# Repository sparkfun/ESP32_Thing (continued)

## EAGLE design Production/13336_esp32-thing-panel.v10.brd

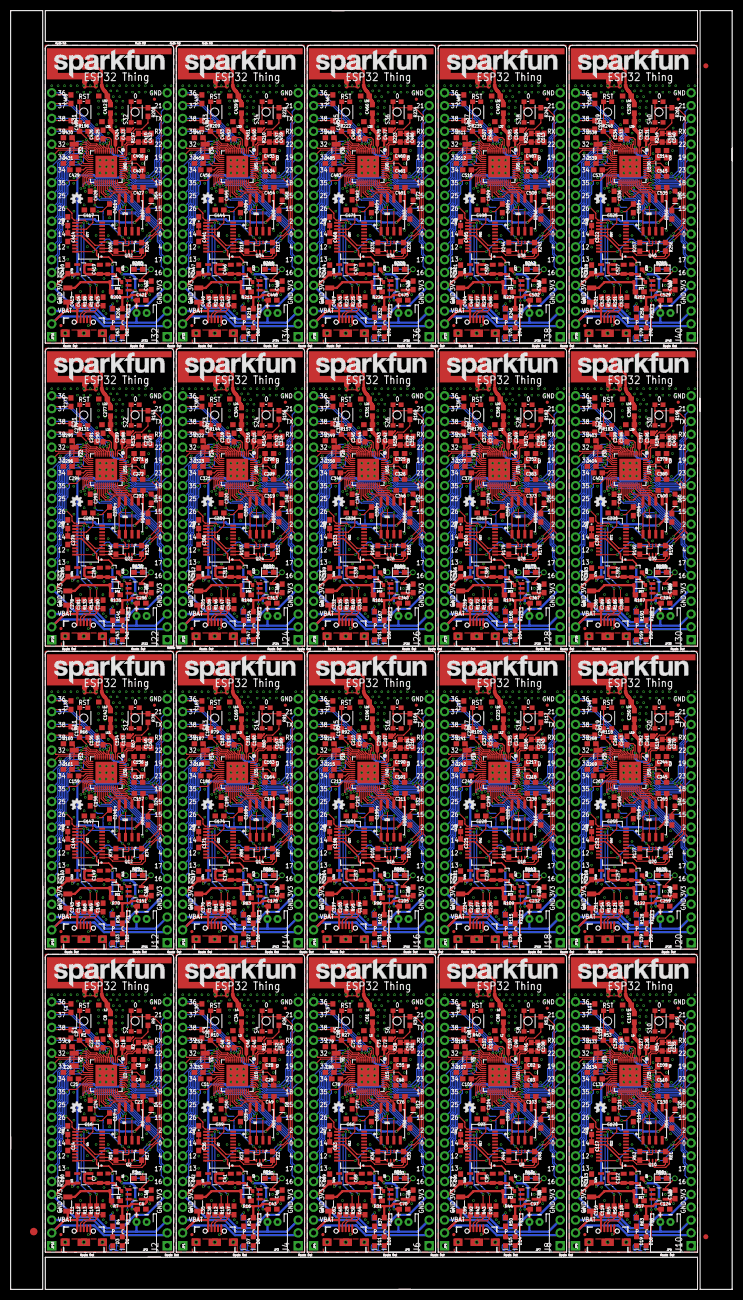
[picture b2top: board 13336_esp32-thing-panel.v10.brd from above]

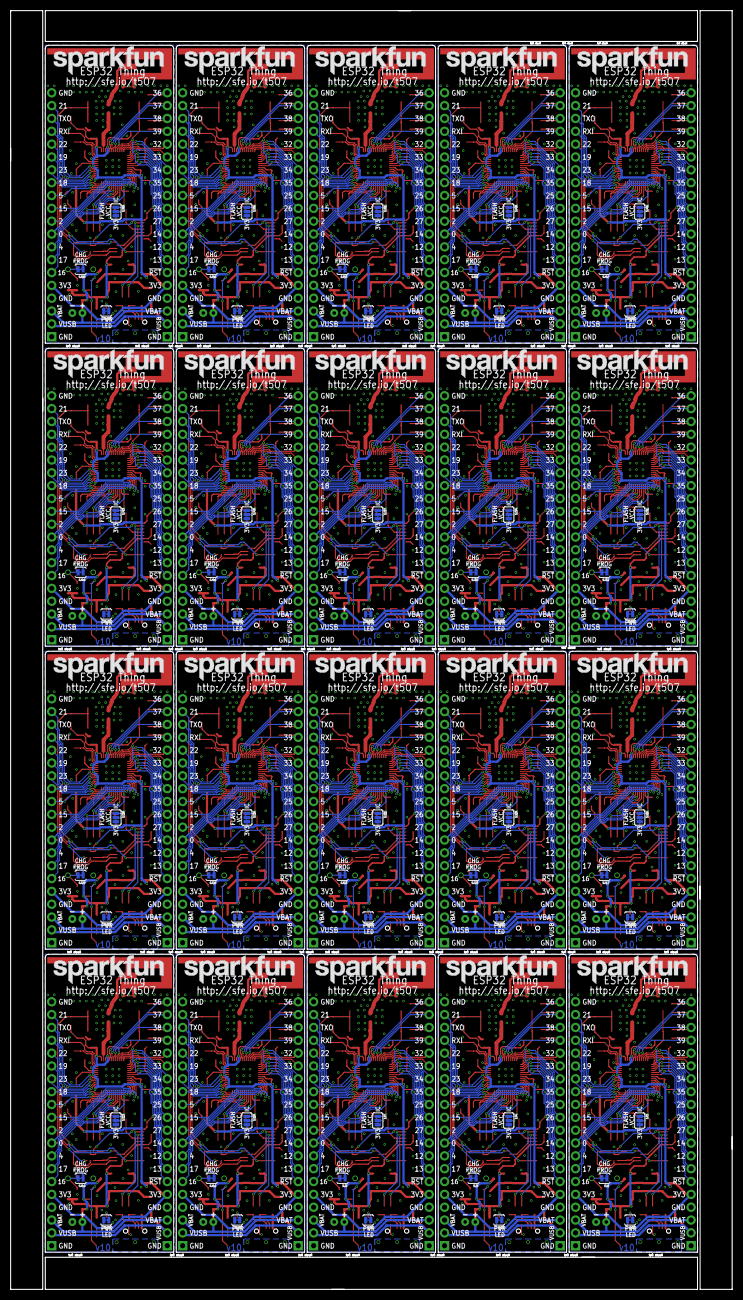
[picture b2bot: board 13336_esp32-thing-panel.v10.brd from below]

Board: 2 copper layers, 142.7 x 253.0 mm, 1423 parts (80 on the bottom side), 1320 nets.

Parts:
C1, C2, C30, C31, C57, C58, C84, C85, C111, C112, C138, C139, C165, C166, C192, C193, C219, C220, C246, C247, C273, C274, C300, C301, C327, C328, C354, C355, C381, C382, C408, C409, C435, C436, C462, C463, C489, C490, C516, C517: 270pF; 0603
C3, C4, C28, C29, C55, C56, C82, C83, C109, C110, C136, C137, C163, C164, C190, C191, C217, C218, C244, C245, C271, C272, C298, C299, C325, C326, C352, C353, C379, C380, C406, C407, C433, C434, C460, C461, C487, C488, C514, C515: 10pF; 0603
C5, C32, C59, C86, C113, C140, C167, C194, C221, C248, C275, C302, C329, C356, C383, C410, C437, C464, C491, C518: 10nF; 0603
C6, C19, C43, C44, C70, C71, C97, C98, C124, C125, C151, C152, C178, C179, C205, C206, C232, C233, C259, C260, C286, C287, C313, C314, C340, C341, C367, C368, C394, C395, C421, C422, C448, C449, C475, C476, C502, C503, C529, C530: 4.7uF; 0603
C7, C41, C68, C95, C122, C149, C176, C203, C230, C257, C284, C311, C338, C365, C392, C419, C446, C473, C500, C527: 1.0uF; 0805
C8, C34, C61, C88, C115, C142, C169, C196, C223, C250, C277, C304, C331, C358, C385, C412, C439, C466, C493, C520: 5.6pF; 0603
C9, C26, C52, C53, C79, C80, C106, C107, C133, C134, C160, C161, C187, C188, C214, C215, C241, C242, C268, C269, C295, C296, C322, C323, C349, C350, C376, C377, C403, C404, C430, C431, C457, C458, C484, C485, C511, C512, C538, C539: 15pF; 0603
C10, C42, C69, C96, C123, C150, C177, C204, C231, C258, C285, C312, C339, C366, C393, C420, C447, C474, C501, C528: 2.2uF; 0603
C11, C14, C16, C17, C20, C21, C23, C25, C33, C35, C36, C39, C46, C47, C49, C51, C60, C62, C63, C66, C73, C74, C76, C78, C87, C89, C90, C93, C100, C101, C103, C105, C114, C116, C117, C120, C127, C128, C130, C132, C141, C143, C144, C147, C154, C155, C157, C159, C168, C170, C171, C174, C181, C182, C184, C186, C195, C197, C198, C201, C208, C209, C211, C213, C222, C224, C225, C228, C235, C236, C238, C240, C249, C251, C252, C255, C262, C263, C265, C267, C276, C278, C279, C282, C289, C290, C292, C294, C303, C305, C306, C309, C316, C317, C319, C321, C330, C332, C333, C336, C343, C344, C346, C348, C357, C359, C360, C363, C370, C371, C373, C375, C384, C386, C387, C390, C397, C398, C400, C402, C411, C413, C414, C417, C424, C425, C427, C429, C438, C440, C441, C444, C451, C452, C454, C456, C465, C467, C468, C471, C478, C479, C481, C483, C492, C494, C495, C498, C505, C506, C508, C510, C519, C521, C522, C525, C532, C533, C535, C537: 0.1uF; 0603
C12, C13, C37, C38, C64, C65, C91, C92, C118, C119, C145, C146, C172, C173, C199, C200, C226, C227, C253, C254, C280, C281, C307, C308, C334, C335, C361, C362, C388, C389, C415, C416, C442, C443, C469, C470, C496, C497, C523, C524: 47pF; 0603
C15, C40, C67, C94, C121, C148, C175, C202, C229, C256, C283, C310, C337, C364, C391, C418, C445, C472, C499, C526: 4.7uF; 0603-CAP
C18, C45, C72, C99, C126, C153, C180, C207, C234, C261, C288, C315, C342, C369, C396, C423, C450, C477, C504, C531: 100pF; 0603
C22, C48, C75, C102, C129, C156, C183, C210, C237, C264, C291, C318, C345, C372, C399, C426, C453, C480, C507, C534: 10uF; 0603
C24, C50, C77, C104, C131, C158, C185, C212, C239, C266, C293, C320, C347, C374, C401, C428, C455, C482, C509, C536: 1.0uF; 0603
C27, C54, C81, C108, C135, C162, C189, C216, C243, C270, C297, C324, C351, C378, C405, C432, C459, C486, C513, C540: 3.0nF; 0603
D1, D6, D10, D14, D18, D22, D26, D30, D34, D38, D42, D46, D50, D54, D58, D62, D66, D70, D74, D78: Yellow; LED-0603
D2, D5, D9, D13, D17, D21, D25, D29, D33, D37, D41, D45, D49, D53, D57, D61, D65, D69, D73, D77: BAT20J; SOD-323
D3, D7, D11, D15, D19, D23, D27, D31, D35, D39, D43, D47, D51, D55, D59, D63, D67, D71, D75, D79: RED; LED-0603
D4, D8, D12, D16, D20, D24, D28, D32, D36, D40, D44, D48, D52, D56, D60, D64, D68, D72, D76, D80: BLUE; LED-0603
E1, E2, E3, E4, E5, E6, E7, E8, E9, E10, E11, E12, E13, E14, E15, E16, E17, E18, E19, E20: ANTENNA; TRACE_ANTENNA_2.4GHZ_25.7MM_TUNED
E$1: FIDUCIAL-1.5X3
E$7, E$8: FIDUCIAL-1X2
F1, F2, F3, F4, F5, F6, F7, F8, F9, F10, F11, F12, F13, F14, F15, F16, F17, F18, F19, F20: 500mA; PTC-1206
FD1, FD2, FD3, FD4, FD5, FD6, FD7, FD8, FD9, FD10, FD11, FD12, FD13, FD14, FD15, FD16, FD17, FD18, FD19, FD20, FD21, FD22, FD23, FD24, FD25, FD26, FD27, FD28, FD29, FD30, FD31, FD32, FD33, FD34, FD35, FD36, FD37, FD38, FD39, FD40: FIDUCIALUFIDUCIAL; MICRO-FIDUCIAL
J1, J2, J3, J4, J5, J6, J7, J8, J9, J10, J11, J12, J13, J14, J15, J16, J17, J18, J19, J20, J21, J22, J23, J24, J25, J26, J27, J28, J29, J30, J31, J32, J33, J34, J35, J36, J37, J38, J39, J40: 1X20_NOSILK
JP1, JP4, JP6, JP8, JP10, JP12, JP14, JP15, JP17, JP19, JP21, JP23, JP25, JP27, JP29, JP31, JP33, JP35, JP37, JP39: USB-B-MICRO-SMD_V03
JP2, JP3, JP5, JP7, JP9, JP11, JP13, JP16, JP18, JP20, JP22, JP24, JP26, JP28, JP30, JP32, JP34, JP36, JP38, JP40: LiPo; JST-2-PTH
L1, L2, L3, L4, L5, L6, L7, L8, L9, L10, L11, L12, L13, L14, L15, L16, L17, L18, L19, L20, L21, L22, L23, L24, L25, L26, L27, L28, L29, L30, L31, L32, L33, L34, L35, L36, L37, L38, L39, L40: DNP; 0603
LOGO1, LOGO3, LOGO4, LOGO6, LOGO7, LOGO9, LOGO10, LOGO12, LOGO13, LOGO15, LOGO16, LOGO18, LOGO19, LOGO21, LOGO22, LOGO24, LOGO25, LOGO27, LOGO28, LOGO30, LOGO31, LOGO33, LOGO34, LOGO36, LOGO37, LOGO39, LOGO40, LOGO42, LOGO43, LOGO45, LOGO46, LOGO48, LOGO49, LOGO51, LOGO52, LOGO54, LOGO55, LOGO57, LOGO58, LOGO60: SFE_LOGO_NAME.2_INCH; SFE_LOGO_NAME_.2
LOGO2, LOGO5, LOGO8, LOGO11, LOGO14, LOGO17, LOGO20, LOGO23, LOGO26, LOGO29, LOGO32, LOGO35, LOGO38, LOGO41, LOGO44, LOGO47, LOGO50, LOGO53, LOGO56, LOGO59: OSHW-LOGOMINI; OSHW-LOGO-MINI
Q1, Q3, Q5, Q7, Q9, Q11, Q13, Q15, Q17, Q19, Q21, Q23, Q25, Q27, Q29, Q31, Q33, Q35, Q37, Q39: 2.5A/30V; SOT23-3
Q2, Q4, Q6, Q8, Q10, Q12, Q14, Q16, Q18, Q20, Q22, Q24, Q26, Q28, Q30, Q32, Q34, Q36, Q38, Q40: MBT3904DW1T1; SC70-6
R1, R7, R9, R10, R16, R17, R18, R22, R23, R26, R27, R31, R35, R36, R39, R40, R44, R48, R49, R52, R53, R57, R61, R62, R65, R66, R70, R74, R75, R78, R79, R83, R87, R88, R91, R92, R96, R100, R101, R104, R105, R109, R113, R114, R117, R118, R122, R126, R127, R130, R131, R135, R139, R140, R143, R144, R148, R152, R153, R156, R157, R161, R165, R166, R169, R170, R174, R178, R179, R182, R183, R187, R191, R192, R195, R196, R200, R204, R205, R208, R209, R213, R217, R218, R221, R222, R226, R230, R231, R234, R235, R239, R243, R244, R247, R248, R252, R256, R257, R260: 10k; 0603
R2, R11, R28, R41, R54, R67, R80, R93, R106, R119, R132, R145, R158, R171, R184, R197, R210, R223, R236, R249: 20k; 0603
R3, R4, R19, R24, R32, R37, R45, R50, R58, R63, R71, R76, R84, R89, R97, R102, R110, R115, R123, R128, R136, R141, R149, R154, R162, R167, R175, R180, R188, R193, R201, R206, R214, R219, R227, R232, R240, R245, R253, R258: 1K; 0603
R5, R21, R34, R47, R60, R73, R86, R99, R112, R125, R138, R151, R164, R177, R190, R203, R216, R229, R242, R255: DNP; 1/6W-RES
R6, R20, R33, R46, R59, R72, R85, R98, R111, R124, R137, R150, R163, R176, R189, R202, R215, R228, R241, R254: 2.0k; 0603
R8, R25, R38, R51, R64, R77, R90, R103, R116, R129, R142, R155, R168, R181, R194, R207, R220, R233, R246, R259: 330; 0603
R12, R13, R14, R15, R29, R30, R42, R43, R55, R56, R68, R69, R81, R82, R94, R95, R107, R108, R120, R121, R133, R134, R146, R147, R159, R160, R172, R173, R185, R186, R198, R199, R211, R212, R224, R225, R237, R238, R250, R251: 27; 0603
S1, S3, S5, S7, S9, S11, S13, S15, S17, S19, S21, S23, S25, S27, S29, S31, S33, S35, S37, S39: RESET; TACTILE_SWITCH_SMD_4.6X2.8MM
S2, S4, S6, S8, S10, S12, S14, S16, S18, S20, S22, S24, S26, S28, S30, S32, S34, S36, S38, S40: BTN-0; TACTILE_SWITCH_SMD_4.6X2.8MM
SJ1, SJ2, SJ5, SJ6, SJ8, SJ9, SJ11, SJ12, SJ14, SJ15, SJ17, SJ18, SJ20, SJ21, SJ23, SJ24, SJ26, SJ27, SJ29, SJ30, SJ32, SJ33, SJ35, SJ36, SJ38, SJ39, SJ41, SJ42, SJ44, SJ45, SJ47, SJ48, SJ50, SJ51, SJ53, SJ54, SJ56, SJ57, SJ59, SJ60: JUMPER-PAD-2-NC_BY_TRACE; PAD-JUMPER-2-NC_BY_TRACE_YES_SILK
SJ3, SJ4, SJ7, SJ10, SJ13, SJ16, SJ19, SJ22, SJ25, SJ28, SJ31, SJ34, SJ37, SJ40, SJ43, SJ46, SJ49, SJ52, SJ55, SJ58: PAD-JUMPER-3-2OF3_NC_BY_TRACE_YES_SILK_FULL_BOX
U1, U8, U13, U18, U23, U28, U33, U38, U43, U48, U53, U58, U63, U68, U73, U78, U83, U88, U93, U98: MCP73831; SOT23-5
U2, U10, U15, U20, U25, U30, U35, U40, U45, U50, U55, U60, U65, U70, U75, U80, U85, U90, U95, U100: ESP3212; QFN48-0.4MM
U3, U9, U14, U19, U24, U29, U34, U39, U44, U49, U54, U59, U64, U69, U74, U79, U84, U89, U94, U99: AP2112K-3.3V; SOT23-5
U4, U7, U12, U17, U22, U27, U32, U37, U42, U47, U52, U57, U62, U67, U72, U77, U82, U87, U92, U97: FT231XS; SSOP20_L
U5, U6, U11, U16, U21, U26, U31, U36, U41, U46, U51, U56, U61, U66, U71, U76, U81, U86, U91, U96: W25Q32FVSS; SOIC-8
Y1, Y3, Y5, Y7, Y9, Y11, Y13, Y15, Y17, Y19, Y21, Y23, Y25, Y27, Y29, Y31, Y33, Y35, Y37, Y39: 26MHz; CRYSTAL-SMD-3.2X2.5
Y2, Y4, Y6, Y8, Y10, Y12, Y14, Y16, Y18, Y20, Y22, Y24, Y26, Y28, Y30, Y32, Y34, Y36, Y38, Y40: 32.768kHz; CRYSTAL-SMD-3.2X1.5MM

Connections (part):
0: J2.9, Q2.6, R9.1, S2.3, S2.4, U2.23
1: J3.14, U10.10
2: J2.10, U2.22
3: J3.13, U10.11
3.3V: C10.1, C18.1, C20.1, C21.1, C22.1, C23.1, C25.1, J1.5, J2.5, R1.2, R9.2, SJ2.2, SJ3.3, U2.1, U2.3, U2.4, U2.19, U2.37, U2.43, U2.46, U3.5
3.3V1: C42.1, C45.1, C46.1, C47.1, C48.1, C49.1, C51.1, J3.5, J4.5, R10.2, R26.2, SJ4.3, SJ6.2, U9.5, U10.1, U10.3, U10.4, U10.19, U10.37, U10.43, U10.46
3.3V2: C69.1, C72.1, C73.1, C74.1, C75.1, C76.1, C78.1, J5.5, J6.5, R27.2, R39.2, SJ7.3, SJ9.2, U14.5, U15.1, U15.3, U15.4, U15.19, U15.37, U15.43, U15.46
3.3V3: C96.1, C99.1, C100.1, C101.1, C102.1, C103.1, C105.1, J7.5, J8.5, R40.2, R52.2, SJ10.3, SJ12.2, U19.5, U20.1, U20.3, U20.4, U20.19, U20.37, U20.43, U20.46
3.3V4: C123.1, C126.1, C127.1, C128.1, C129.1, C130.1, C132.1, J9.5, J10.5, R53.2, R65.2, SJ13.3, SJ15.2, U24.5, U25.1, U25.3, U25.4, U25.19, U25.37, U25.43, U25.46
3.3V5: C150.1, C153.1, C154.1, C155.1, C156.1, C157.1, C159.1, J11.5, J12.5, R66.2, R78.2, SJ16.3, SJ18.2, U29.5, U30.1, U30.3, U30.4, U30.19, U30.37, U30.43, U30.46
3.3V6: C177.1, C180.1, C181.1, C182.1, C183.1, C184.1, C186.1, J13.5, J14.5, R79.2, R91.2, SJ19.3, SJ21.2, U34.5, U35.1, U35.3, U35.4, U35.19, U35.37, U35.43, U35.46
3.3V7: C204.1, C207.1, C208.1, C209.1, C210.1, C211.1, C213.1, J15.5, J16.5, R92.2, R104.2, SJ22.3, SJ24.2, U39.5, U40.1, U40.3, U40.4, U40.19, U40.37, U40.43, U40.46
3.3V8: C231.1, C234.1, C235.1, C236.1, C237.1, C238.1, C240.1, J17.5, J18.5, R105.2, R117.2, SJ25.3, SJ27.2, U44.5, U45.1, U45.3, U45.4, U45.19, U45.37, U45.43, U45.46
3.3V9: C258.1, C261.1, C262.1, C263.1, C264.1, C265.1, C267.1, J19.5, J20.5, R118.2, R130.2, SJ28.3, SJ30.2, U49.5, U50.1, U50.3, U50.4, U50.19, U50.37, U50.43, U50.46
3.3V10: C285.1, C288.1, C289.1, C290.1, C291.1, C292.1, C294.1, J21.5, J22.5, R131.2, R143.2, SJ31.3, SJ33.2, U54.5, U55.1, U55.3, U55.4, U55.19, U55.37, U55.43, U55.46
3.3V11: C312.1, C315.1, C316.1, C317.1, C318.1, C319.1, C321.1, J23.5, J24.5, R144.2, R156.2, SJ34.3, SJ36.2, U59.5, U60.1, U60.3, U60.4, U60.19, U60.37, U60.43, U60.46
3.3V12: C339.1, C342.1, C343.1, C344.1, C345.1, C346.1, C348.1, J25.5, J26.5, R157.2, R169.2, SJ37.3, SJ39.2, U64.5, U65.1, U65.3, U65.4, U65.19, U65.37, U65.43, U65.46
3.3V13: C366.1, C369.1, C370.1, C371.1, C372.1, C373.1, C375.1, J27.5, J28.5, R170.2, R182.2, SJ40.3, SJ42.2, U69.5, U70.1, U70.3, U70.4, U70.19, U70.37, U70.43, U70.46
3.3V14: C393.1, C396.1, C397.1, C398.1, C399.1, C400.1, C402.1, J29.5, J30.5, R183.2, R195.2, SJ43.3, SJ45.2, U74.5, U75.1, U75.3, U75.4, U75.19, U75.37, U75.43, U75.46
3.3V15: C420.1, C423.1, C424.1, C425.1, C426.1, C427.1, C429.1, J31.5, J32.5, R196.2, R208.2, SJ46.3, SJ48.2, U79.5, U80.1, U80.3, U80.4, U80.19, U80.37, U80.43, U80.46
3.3V16: C447.1, C450.1, C451.1, C452.1, C453.1, C454.1, C456.1, J33.5, J34.5, R209.2, R221.2, SJ49.3, SJ51.2, U84.5, U85.1, U85.3, U85.4, U85.19, U85.37, U85.43, U85.46
3.3V17: C474.1, C477.1, C478.1, C479.1, C480.1, C481.1, C483.1, J35.5, J36.5, R222.2, R234.2, SJ52.3, SJ54.2, U89.5, U90.1, U90.3, U90.4, U90.19, U90.37, U90.43, U90.46
3.3V18: C501.1, C504.1, C505.1, C506.1, C507.1, C508.1, C510.1, J37.5, J38.5, R235.2, R247.2, SJ55.3, SJ57.2, U94.5, U95.1, U95.3, U95.4, U95.19, U95.37, U95.43, U95.46
3.3V19: C528.1, C531.1, C532.1, C533.1, C534.1, C535.1, C537.1, J39.5, J40.5, R248.2, R260.2, SJ58.3, SJ60.2, U99.5, U100.1, U100.3, U100.4, U100.19, U100.37, U100.43, U100.46
3.3V_F: C16.1, U4.3, U4.13, U4.14
3.3V_F1: C39.1, U7.3, U7.13, U7.14
3.3V_F2: C66.1, U12.3, U12.13, U12.14
3.3V_F3: C93.1, U17.3, U17.13, U17.14
3.3V_F4: C120.1, U22.3, U22.13, U22.14
3.3V_F5: C147.1, U27.3, U27.13, U27.14
3.3V_F6: C174.1, U32.3, U32.13, U32.14
3.3V_F7: C201.1, U37.3, U37.13, U37.14
3.3V_F8: C228.1, U42.3, U42.13, U42.14
3.3V_F9: C255.1, U47.3, U47.13, U47.14
3.3V_F10: C282.1, U52.3, U52.13, U52.14
3.3V_F11: C309.1, U57.3, U57.13, U57.14
3.3V_F12: C336.1, U62.3, U62.13, U62.14
3.3V_F13: C363.1, U67.3, U67.13, U67.14
3.3V_F14: C390.1, U72.3, U72.13, U72.14
3.3V_F15: C417.1, U77.3, U77.13, U77.14
3.3V_F16: C444.1, U82.3, U82.13, U82.14
3.3V_F17: C471.1, U87.3, U87.13, U87.14
3.3V_F18: C498.1, U92.3, U92.13, U92.14
3.3V_F19: C525.1, U97.3, U97.13, U97.14
4: J2.8, U2.24
5: D4.A, J2.12, U2.34
6: C31.2, J3.17, U10.8
7: C31.1, J3.18, U10.7
8: C30.2, J3.20, U10.5
9: C30.1, J3.19, U10.6
10: J4.11, U10.21
11: J3.9, U10.17
12: J1.8, U2.18
13: J1.7, U2.20
14: J1.9, U2.17
15: J2.11, U2.21
16: J2.6, U2.25
17: J2.7, U2.27
18: J2.13, U2.35
19: J2.15, U2.38
20: J3.7, U10.20
21: J2.19, U2.42
22: J2.16, U2.39
23: J2.14, U2.36
24: J3.8, U10.18
25: J1.12, U2.14
26: J1.11, U2.15
27: J1.10, U2.16
28: J3.10, U10.16
29: J3.11, U10.15
30: J4.16, U10.39
31: J4.19, U10.42
32: J4.15, U10.38
32K_XN: C26.2, J1.15, U2.13, Y2.P$2
32K_XN1: C53.2, J3.15, U10.13, Y4.P$2
32K_XN2: C80.2, J5.15, U15.13, Y6.P$2
32K_XN3: C107.2, J7.15, U20.13, Y8.P$2
32K_XN4: C134.2, J9.15, U25.13, Y10.P$2
32K_XN5: C161.2, J11.15, U30.13, Y12.P$2
32K_XN6: C188.2, J13.15, U35.13, Y14.P$2
32K_XN7: C215.2, J15.15, U40.13, Y16.P$2
32K_XN8: C242.2, J17.15, U45.13, Y18.P$2
32K_XN9: C269.2, J19.15, U50.13, Y20.P$2
32K_XN10: C296.2, J21.15, U55.13, Y22.P$2
32K_XN11: C323.2, J23.15, U60.13, Y24.P$2
32K_XN12: C350.2, J25.15, U65.13, Y26.P$2
32K_XN13: C377.2, J27.15, U70.13, Y28.P$2
32K_XN14: C404.2, J29.15, U75.13, Y30.P$2
32K_XN15: C431.2, J31.15, U80.13, Y32.P$2
32K_XN16: C458.2, J33.15, U85.13, Y34.P$2
32K_XN17: C485.2, J35.15, U90.13, Y36.P$2
32K_XN18: C512.2, J37.15, U95.13, Y38.P$2
32K_XN19: C539.2, J39.15, U100.13, Y40.P$2
32K_XP: C9.2, J1.16, U2.12, Y2.P$1
32K_XP1: C52.2, J3.16, U10.12, Y4.P$1
32K_XP2: C79.2, J5.16, U15.12, Y6.P$1
32K_XP3: C106.2, J7.16, U20.12, Y8.P$1
32K_XP4: C133.2, J9.16, U25.12, Y10.P$1
32K_XP5: C160.2, J11.16, U30.12, Y12.P$1
32K_XP6: C187.2, J13.16, U35.12, Y14.P$1
32K_XP7: C214.2, J15.16, U40.12, Y16.P$1
32K_XP8: C241.2, J17.16, U45.12, Y18.P$1
32K_XP9: C268.2, J19.16, U50.12, Y20.P$1
32K_XP10: C295.2, J21.16, U55.12, Y22.P$1
32K_XP11: C322.2, J23.16, U60.12, Y24.P$1
32K_XP12: C349.2, J25.16, U65.12, Y26.P$1
32K_XP13: C376.2, J27.16, U70.12, Y28.P$1
32K_XP14: C403.2, J29.16, U75.12, Y30.P$1
32K_XP15: C430.2, J31.16, U80.12, Y32.P$1
32K_XP16: C457.2, J33.16, U85.12, Y34.P$1
32K_XP17: C484.2, J35.16, U90.12, Y36.P$1
32K_XP18: C511.2, J37.16, U95.12, Y38.P$1
32K_XP19: C538.2, J39.16, U100.12, Y40.P$1
33: J4.13, U10.35
34: J1.14, U2.10
35: J1.13, U2.11
36: C1.2, J1.20, U2.5
37: C1.1, J1.19, U2.6
38: C2.1, J1.18, U2.7
39: C2.2, J1.17, U2.8
40: J4.6, U10.25
41: D8.A, J4.12, U10.34
42: J4.8, U10.24
43: J4.10, U10.22
44: J3.12, U10.14
45: J4.9, Q4.6, R26.1, S4.3, S4.4, U10.23
46: J4.7, U10.27
47: J4.14, U10.36
48: J5.14, U15.10
49: J5.13, U15.11
50: C58.2, J5.17, U15.8
51: C58.1, J5.18, U15.7
52: C57.2, J5.20, U15.5
53: C57.1, J5.19, U15.6
54: J6.11, U15.21
55: J5.9, U15.17
56: J5.7, U15.20
57: J5.8, U15.18
58: J5.10, U15.16
59: J5.11, U15.15
60: J6.16, U15.39
61: J6.19, U15.42
62: J6.15, U15.38
63: J6.13, U15.35
64: J6.6, U15.25
65: D12.A, J6.12, U15.34
66: J6.8, U15.24
67: J6.10, U15.22
68: J5.12, U15.14
69: J6.9, Q6.6, R39.1, S6.3, S6.4, U15.23
70: J6.7, U15.27
71: J6.14, U15.36
72: J7.14, U20.10
73: J7.13, U20.11
74: C85.2, J7.17, U20.8
75: C85.1, J7.18, U20.7
76: C84.2, J7.20, U20.5
77: C84.1, J7.19, U20.6
78: J8.11, U20.21
79: J7.9, U20.17
80: J7.7, U20.20
81: J7.8, U20.18
82: J7.10, U20.16
83: J7.11, U20.15
84: J8.16, U20.39
85: J8.19, U20.42
86: J8.15, U20.38
87: J8.13, U20.35
88: J8.6, U20.25
89: D16.A, J8.12, U20.34
90: J8.8, U20.24
91: J8.10, U20.22
92: J7.12, U20.14
93: J8.9, Q8.6, R52.1, S8.3, S8.4, U20.23
94: J8.7, U20.27
95: J8.14, U20.36
96: J9.14, U25.10
97: J9.13, U25.11
98: C112.2, J9.17, U25.8
99: C112.1, J9.18, U25.7
100: C111.2, J9.20, U25.5
101: C111.1, J9.19, U25.6
102: J10.11, U25.21
103: J9.9, U25.17
104: J9.7, U25.20
105: J9.8, U25.18
106: J9.10, U25.16
107: J9.11, U25.15
108: J10.16, U25.39
109: J10.19, U25.42
110: J10.15, U25.38
111: J10.13, U25.35
112: J10.6, U25.25
113: D20.A, J10.12, U25.34
114: J10.8, U25.24
115: J10.10, U25.22
116: J9.12, U25.14
117: J10.9, Q10.6, R65.1, S10.3, S10.4, U25.23
118: J10.7, U25.27
119: J10.14, U25.36
120: J11.14, U30.10
121: J11.13, U30.11
122: C139.2, J11.17, U30.8
123: C139.1, J11.18, U30.7
124: C138.2, J11.20, U30.5
125: C138.1, J11.19, U30.6
126: J12.11, U30.21
127: J11.9, U30.17
128: J11.7, U30.20
129: J11.8, U30.18
130: J11.10, U30.16
131: J11.11, U30.15
132: J12.16, U30.39
133: J12.19, U30.42
134: J12.15, U30.38
135: J12.13, U30.35
136: J12.6, U30.25
137: D24.A, J12.12, U30.34
138: J12.8, U30.24
139: J12.10, U30.22
140: J11.12, U30.14
141: J12.9, Q12.6, R78.1, S12.3, S12.4, U30.23
142: J12.7, U30.27
143: J12.14, U30.36
144: J13.14, U35.10
145: J13.13, U35.11
146: C166.2, J13.17, U35.8
147: C166.1, J13.18, U35.7
148: C165.2, J13.20, U35.5
149: C165.1, J13.19, U35.6
150: J14.11, U35.21
151: J13.9, U35.17
152: J13.7, U35.20
153: J13.8, U35.18
154: J13.10, U35.16
155: J13.11, U35.15
156: J14.16, U35.39
157: J14.19, U35.42
158: J14.15, U35.38
159: J14.13, U35.35
160: J14.6, U35.25
161: D28.A, J14.12, U35.34
162: J14.8, U35.24
163: J14.10, U35.22
164: J13.12, U35.14
165: J14.9, Q14.6, R91.1, S14.3, S14.4, U35.23
166: J14.7, U35.27
167: J14.14, U35.36
168: J15.14, U40.10
169: J15.13, U40.11
170: C193.2, J15.17, U40.8
171: C193.1, J15.18, U40.7
172: C192.2, J15.20, U40.5
173: C192.1, J15.19, U40.6
174: J16.11, U40.21
175: J15.9, U40.17
176: J15.7, U40.20
177: J15.8, U40.18
178: J15.10, U40.16
179: J15.11, U40.15
180: J16.16, U40.39
181: J16.19, U40.42
182: J16.15, U40.38
183: J16.13, U40.35
184: J16.6, U40.25
185: D32.A, J16.12, U40.34
186: J16.8, U40.24
187: J16.10, U40.22
188: J15.12, U40.14
189: J16.9, Q16.6, R104.1, S16.3, S16.4, U40.23
190: J16.7, U40.27
191: J16.14, U40.36
192: J17.14, U45.10
193: J17.13, U45.11
194: C220.2, J17.17, U45.8
195: C220.1, J17.18, U45.7
196: C219.2, J17.20, U45.5
197: C219.1, J17.19, U45.6
198: J18.11, U45.21
199: J17.9, U45.17
200: J17.7, U45.20
201: J17.8, U45.18
202: J17.10, U45.16
203: J17.11, U45.15
204: J18.16, U45.39
205: J18.19, U45.42
206: J18.15, U45.38
207: J18.13, U45.35
208: J18.6, U45.25
209: D36.A, J18.12, U45.34
210: J18.8, U45.24
211: J18.10, U45.22
212: J17.12, U45.14
213: J18.9, Q18.6, R117.1, S18.3, S18.4, U45.23
214: J18.7, U45.27
215: J18.14, U45.36
216: J19.14, U50.10
217: J19.13, U50.11
218: C247.2, J19.17, U50.8
219: C247.1, J19.18, U50.7
220: C246.2, J19.20, U50.5
221: C246.1, J19.19, U50.6
222: J20.11, U50.21
223: J19.9, U50.17
224: J19.7, U50.20
225: J19.8, U50.18
226: J19.10, U50.16
227: J19.11, U50.15
228: J20.16, U50.39
229: J20.19, U50.42
230: J20.15, U50.38
231: J20.13, U50.35
232: J20.6, U50.25
233: D40.A, J20.12, U50.34
234: J20.8, U50.24
235: J20.10, U50.22
236: J19.12, U50.14
237: J20.9, Q20.6, R130.1, S20.3, S20.4, U50.23
238: J20.7, U50.27
239: J20.14, U50.36
240: J21.14, U55.10
241: J21.13, U55.11
242: C274.2, J21.17, U55.8
243: C274.1, J21.18, U55.7
244: C273.2, J21.20, U55.5
245: C273.1, J21.19, U55.6
246: J22.11, U55.21
247: J21.9, U55.17
248: J21.7, U55.20
249: J21.8, U55.18
250: J21.10, U55.16
251: J21.11, U55.15
252: J22.16, U55.39
253: J22.19, U55.42
254: J22.15, U55.38
255: J22.13, U55.35
256: J22.6, U55.25
257: D44.A, J22.12, U55.34
258: J22.8, U55.24
259: J22.10, U55.22
260: J21.12, U55.14
261: J22.9, Q22.6, R143.1, S22.3, S22.4, U55.23
262: J22.7, U55.27
263: J22.14, U55.36
264: J23.14, U60.10
265: J23.13, U60.11
266: C301.2, J23.17, U60.8
267: C301.1, J23.18, U60.7
268: C300.2, J23.20, U60.5
269: C300.1, J23.19, U60.6
270: J24.11, U60.21
271: J23.9, U60.17
272: J23.7, U60.20
273: J23.8, U60.18
274: J23.10, U60.16
275: J23.11, U60.15
276: J24.16, U60.39
277: J24.19, U60.42
278: J24.15, U60.38
279: J24.13, U60.35
280: J24.6, U60.25
281: D48.A, J24.12, U60.34
282: J24.8, U60.24
283: J24.10, U60.22
284: J23.12, U60.14
285: J24.9, Q24.6, R156.1, S24.3, S24.4, U60.23
286: J24.7, U60.27
287: J24.14, U60.36
288: J25.14, U65.10
289: J25.13, U65.11
290: C328.2, J25.17, U65.8
291: C328.1, J25.18, U65.7
292: C327.2, J25.20, U65.5
293: C327.1, J25.19, U65.6
294: J26.11, U65.21
295: J25.9, U65.17
296: J25.7, U65.20
297: J25.8, U65.18
298: J25.10, U65.16
299: J25.11, U65.15
300: J26.16, U65.39
301: J26.19, U65.42
302: J26.15, U65.38
303: J26.13, U65.35
304: J26.6, U65.25
305: D52.A, J26.12, U65.34
306: J26.8, U65.24
307: J26.10, U65.22
308: J25.12, U65.14
309: J26.9, Q26.6, R169.1, S26.3, S26.4, U65.23
310: J26.7, U65.27
311: J26.14, U65.36
312: J27.14, U70.10
313: J27.13, U70.11
314: C355.2, J27.17, U70.8
315: C355.1, J27.18, U70.7
316: C354.2, J27.20, U70.5
317: C354.1, J27.19, U70.6
318: J28.11, U70.21
319: J27.9, U70.17
320: J27.7, U70.20
321: J27.8, U70.18
322: J27.10, U70.16
323: J27.11, U70.15
324: J28.16, U70.39
325: J28.19, U70.42
326: J28.15, U70.38
327: J28.13, U70.35
328: J28.6, U70.25
329: D56.A, J28.12, U70.34
330: J28.8, U70.24
331: J28.10, U70.22
332: J27.12, U70.14
333: J28.9, Q28.6, R182.1, S28.3, S28.4, U70.23
334: J28.7, U70.27
335: J28.14, U70.36
336: J29.14, U75.10
337: J29.13, U75.11
338: C382.2, J29.17, U75.8
339: C382.1, J29.18, U75.7
340: C381.2, J29.20, U75.5
341: C381.1, J29.19, U75.6
342: J30.11, U75.21
343: J29.9, U75.17
344: J29.7, U75.20
345: J29.8, U75.18
346: J29.10, U75.16
347: J29.11, U75.15
348: J30.16, U75.39
349: J30.19, U75.42
350: J30.15, U75.38
351: J30.13, U75.35
352: J30.6, U75.25
353: D60.A, J30.12, U75.34
354: J30.8, U75.24
355: J30.10, U75.22
356: J29.12, U75.14
357: J30.9, Q30.6, R195.1, S30.3, S30.4, U75.23
358: J30.7, U75.27
359: J30.14, U75.36
360: J31.14, U80.10
361: J31.13, U80.11
362: C409.2, J31.17, U80.8
363: C409.1, J31.18, U80.7
364: C408.2, J31.20, U80.5
365: C408.1, J31.19, U80.6
366: J32.11, U80.21
367: J31.9, U80.17
368: J31.7, U80.20
369: J31.8, U80.18
370: J31.10, U80.16
371: J31.11, U80.15
372: J32.16, U80.39
373: J32.19, U80.42
374: J32.15, U80.38
375: J32.13, U80.35
376: J32.6, U80.25
377: D64.A, J32.12, U80.34
378: J32.8, U80.24
379: J32.10, U80.22
380: J31.12, U80.14
381: J32.9, Q32.6, R208.1, S32.3, S32.4, U80.23
382: J32.7, U80.27
383: J32.14, U80.36
384: J33.14, U85.10
385: J33.13, U85.11
386: C436.2, J33.17, U85.8
387: C436.1, J33.18, U85.7
388: C435.2, J33.20, U85.5
389: C435.1, J33.19, U85.6
390: J34.11, U85.21
391: J33.9, U85.17
392: J33.7, U85.20
393: J33.8, U85.18
394: J33.10, U85.16
395: J33.11, U85.15
396: J34.16, U85.39
397: J34.19, U85.42
398: J34.15, U85.38
399: J34.13, U85.35
400: J34.6, U85.25
401: D68.A, J34.12, U85.34
402: J34.8, U85.24
403: J34.10, U85.22
404: J33.12, U85.14
405: J34.9, Q34.6, R221.1, S34.3, S34.4, U85.23
406: J34.7, U85.27
407: J34.14, U85.36
408: J35.14, U90.10
409: J35.13, U90.11
410: C463.2, J35.17, U90.8
411: C463.1, J35.18, U90.7
412: C462.2, J35.20, U90.5
413: C462.1, J35.19, U90.6
414: J36.11, U90.21
415: J35.9, U90.17
416: J35.7, U90.20
417: J35.8, U90.18
418: J35.10, U90.16
419: J35.11, U90.15
420: J36.16, U90.39
421: J36.19, U90.42
422: J36.15, U90.38
423: J36.13, U90.35
424: J36.6, U90.25
425: D72.A, J36.12, U90.34
426: J36.8, U90.24
427: J36.10, U90.22
428: J35.12, U90.14
429: J36.9, Q36.6, R234.1, S36.3, S36.4, U90.23
430: J36.7, U90.27
431: J36.14, U90.36
432: J37.14, U95.10
433: J37.13, U95.11
434: C490.2, J37.17, U95.8
435: C490.1, J37.18, U95.7
436: C489.2, J37.20, U95.5
437: C489.1, J37.19, U95.6
438: J38.11, U95.21
439: J37.9, U95.17
440: J37.7, U95.20
441: J37.8, U95.18
442: J37.10, U95.16
443: J37.11, U95.15
444: J38.16, U95.39
445: J38.19, U95.42
446: J38.15, U95.38
447: J38.13, U95.35
448: J38.6, U95.25
449: D76.A, J38.12, U95.34
450: J38.8, U95.24
451: J38.10, U95.22
452: J37.12, U95.14
453: J38.9, Q38.6, R247.1, S38.3, S38.4, U95.23
454: J38.7, U95.27
455: J38.14, U95.36
456: J39.14, U100.10
457: J39.13, U100.11
458: C517.2, J39.17, U100.8
459: C517.1, J39.18, U100.7
460: C516.2, J39.20, U100.5
461: C516.1, J39.19, U100.6
462: J40.11, U100.21
463: J39.9, U100.17
464: J39.7, U100.20
465: J39.8, U100.18
466: J39.10, U100.16
467: J39.11, U100.15
468: J40.16, U100.39
469: J40.19, U100.42
470: J40.15, U100.38
471: J40.13, U100.35
472: J40.6, U100.25
473: D80.A, J40.12, U100.34
474: J40.8, U100.24
475: J40.10, U100.22
476: J39.12, U100.14
477: J40.9, Q40.6, R260.1, S40.3, S40.4, U100.23
478: J40.7, U100.27
479: J40.14, U100.36
CAP_10N: C5.2, C27.1, R2.2, U2.48
CAP_10N1: C32.2, C54.1, R11.2, U10.48
CAP_10N2: C59.2, C81.1, R28.2, U15.48
CAP_10N3: C86.2, C108.1, R41.2, U20.48
CAP_10N4: C113.2, C135.1, R54.2, U25.48
CAP_10N5: C140.2, C162.1, R67.2, U30.48
CAP_10N6: C167.2, C189.1, R80.2, U35.48
CAP_10N7: C194.2, C216.1, R93.2, U40.48
CAP_10N8: C221.2, C243.1, R106.2, U45.48
CAP_10N9: C248.2, C270.1, R119.2, U50.48
CAP_10N10: C275.2, C297.1, R132.2, U55.48
CAP_10N11: C302.2, C324.1, R145.2, U60.48
CAP_10N12: C329.2, C351.1, R158.2, U65.48
CAP_10N13: C356.2, C378.1, R171.2, U70.48
CAP_10N14: C383.2, C405.1, R184.2, U75.48
CAP_10N15: C410.2, C432.1, R197.2, U80.48
CAP_10N16: C437.2, C459.1, R210.2, U85.48
CAP_10N17: C464.2, C486.1, R223.2, U90.48
CAP_10N18: C491.2, C513.1, R236.2, U95.48
CAP_10N19: C518.2, C540.1, R249.2, U100.48
CHIP_PU: J1.6, Q2.3, R1.1, S1.3, S1.4, U2.9
CHIP_PU1: J3.6, Q4.3, R10.1, S3.3, S3.4, U10.9
CHIP_PU2: J5.6, Q6.3, R27.1, S5.3, S5.4, U15.9
CHIP_PU3: J7.6, Q8.3, R40.1, S7.3, S7.4, U20.9
CHIP_PU4: J9.6, Q10.3, R53.1, S9.3, S9.4, U25.9
CHIP_PU5: J11.6, Q12.3, R66.1, S11.3, S11.4, U30.9
CHIP_PU6: J13.6, Q14.3, R79.1, S13.3, S13.4, U35.9
CHIP_PU7: J15.6, Q16.3, R92.1, S15.3, S15.4, U40.9
CHIP_PU8: J17.6, Q18.3, R105.1, S17.3, S17.4, U45.9
CHIP_PU9: J19.6, Q20.3, R118.1, S19.3, S19.4, U50.9
CHIP_PU10: J21.6, Q22.3, R131.1, S21.3, S21.4, U55.9
CHIP_PU11: J23.6, Q24.3, R144.1, S23.3, S23.4, U60.9
CHIP_PU12: J25.6, Q26.3, R157.1, S25.3, S25.4, U65.9
CHIP_PU13: J27.6, Q28.3, R170.1, S27.3, S27.4, U70.9
CHIP_PU14: J29.6, Q30.3, R183.1, S29.3, S29.4, U75.9
CHIP_PU15: J31.6, Q32.3, R196.1, S31.3, S31.4, U80.9
CHIP_PU16: J33.6, Q34.3, R209.1, S33.3, S33.4, U85.9
CHIP_PU17: J35.6, Q36.3, R222.1, S35.3, S35.4, U90.9
CHIP_PU18: J37.6, Q38.3, R235.1, S37.3, S37.4, U95.9
CHIP_PU19: J39.6, Q40.3, R248.1, S39.3, S39.4, U100.9
D+: C13.1, JP15.D+, R14.1
D+1: C37.1, JP1.D+, R15.1
D+2: C64.1, JP4.D+, R30.1
D+3: C91.1, JP6.D+, R43.1
D+4: C118.1, JP8.D+, R56.1
D+5: C145.1, JP10.D+, R69.1
D+6: C172.1, JP12.D+, R82.1
D+7: C199.1, JP14.D+, R95.1
D+8: C226.1, JP17.D+, R108.1
D+9: C253.1, JP19.D+, R121.1
D+10: C280.1, JP21.D+, R134.1
D+11: C307.1, JP23.D+, R147.1
D+12: C334.1, JP25.D+, R160.1
D+13: C361.1, JP27.D+, R173.1
D+14: C388.1, JP29.D+, R186.1
D+15: C415.1, JP31.D+, R199.1
D+16: C442.1, JP33.D+, R212.1
D+17: C469.1, JP35.D+, R225.1
D+18: C496.1, JP37.D+, R238.1
D+19: C523.1, JP39.D+, R251.1
D-: C12.1, JP15.D-, R13.1
D-1: C38.1, JP1.D-, R12.1
D-2: C65.1, JP4.D-, R29.1
D-3: C92.1, JP6.D-, R42.1
D-4: C119.1, JP8.D-, R55.1
D-5: C146.1, JP10.D-, R68.1
D-6: C173.1, JP12.D-, R81.1
D-7: C200.1, JP14.D-, R94.1
D-8: C227.1, JP17.D-, R107.1
D-9: C254.1, JP19.D-, R120.1
D-10: C281.1, JP21.D-, R133.1
D-11: C308.1, JP23.D-, R146.1
D-12: C335.1, JP25.D-, R159.1
D-13: C362.1, JP27.D-, R172.1
D-14: C389.1, JP29.D-, R185.1
D-15: C416.1, JP31.D-, R198.1
D-16: C443.1, JP33.D-, R211.1
D-17: C470.1, JP35.D-, R224.1
D-18: C497.1, JP37.D-, R237.1
D-19: C524.1, JP39.D-, R250.1
DTR: Q2.1, R17.1, U4.1
DTR1: Q4.1, R22.1, U7.1
DTR2: Q6.1, R35.1, U12.1
DTR3: Q8.1, R48.1, U17.1
DTR4: Q10.1, R61.1, U22.1
DTR5: Q12.1, R74.1, U27.1
DTR6: Q14.1, R87.1, U32.1
DTR7: Q16.1, R100.1, U37.1
DTR8: Q18.1, R113.1, U42.1
DTR9: Q20.1, R126.1, U47.1
DTR10: Q22.1, R139.1, U52.1
DTR11: Q24.1, R152.1, U57.1
DTR12: Q26.1, R165.1, U62.1
DTR13: Q28.1, R178.1, U67.1
DTR14: Q30.1, R191.1, U72.1
DTR15: Q32.1, R204.1, U77.1
DTR16: Q34.1, R217.1, U82.1
DTR17: Q36.1, R230.1, U87.1
DTR18: Q38.1, R243.1, U92.1
DTR19: Q40.1, R256.1, U97.1
FLASH_SCK: U2.31, U5.6
FLASH_SCK1: U6.6, U10.31
FLASH_SCK2: U11.6, U15.31
FLASH_SCK3: U16.6, U20.31
FLASH_SCK4: U21.6, U25.31
FLASH_SCK5: U26.6, U30.31
FLASH_SCK6: U31.6, U35.31
FLASH_SCK7: U36.6, U40.31
FLASH_SCK8: U41.6, U45.31
FLASH_SCK9: U46.6, U50.31
FLASH_SCK10: U51.6, U55.31
FLASH_SCK11: U56.6, U60.31
FLASH_SCK12: U61.6, U65.31
FLASH_SCK13: U66.6, U70.31
FLASH_SCK14: U71.6, U75.31
FLASH_SCK15: U76.6, U80.31
FLASH_SCK16: U81.6, U85.31
FLASH_SCK17: U86.6, U90.31
FLASH_SCK18: U91.6, U95.31
FLASH_SCK19: U96.6, U100.31
FLASH_SCS: U2.30, U5.1
FLASH_SCS1: U6.1, U10.30
FLASH_SCS2: U11.1, U15.30
FLASH_SCS3: U16.1, U20.30
FLASH_SCS4: U21.1, U25.30
FLASH_SCS5: U26.1, U30.30
FLASH_SCS6: U31.1, U35.30
FLASH_SCS7: U36.1, U40.30
FLASH_SCS8: U41.1, U45.30
FLASH_SCS9: U46.1, U50.30
FLASH_SCS10: U51.1, U55.30
FLASH_SCS11: U56.1, U60.30
FLASH_SCS12: U61.1, U65.30
FLASH_SCS13: U66.1, U70.30
FLASH_SCS14: U71.1, U75.30
FLASH_SCS15: U76.1, U80.30
FLASH_SCS16: U81.1, U85.30
FLASH_SCS17: U86.1, U90.30
FLASH_SCS18: U91.1, U95.30
FLASH_SCS19: U96.1, U100.30
FLASH_SDI: U2.33, U5.5
FLASH_SDI1: U6.5, U10.33
FLASH_SDI2: U11.5, U15.33
FLASH_SDI3: U16.5, U20.33
FLASH_SDI4: U21.5, U25.33
FLASH_SDI5: U26.5, U30.33
FLASH_SDI6: U31.5, U35.33
FLASH_SDI7: U36.5, U40.33
FLASH_SDI8: U41.5, U45.33
FLASH_SDI9: U46.5, U50.33
FLASH_SDI10: U51.5, U55.33
FLASH_SDI11: U56.5, U60.33
FLASH_SDI12: U61.5, U65.33
FLASH_SDI13: U66.5, U70.33
FLASH_SDI14: U71.5, U75.33
FLASH_SDI15: U76.5, U80.33
FLASH_SDI16: U81.5, U85.33
FLASH_SDI17: U86.5, U90.33
FLASH_SDI18: U91.5, U95.33
FLASH_SDI19: U96.5, U100.33
FLASH_SDO: U2.32, U5.2
FLASH_SDO1: U6.2, U10.32
FLASH_SDO2: U11.2, U15.32
FLASH_SDO3: U16.2, U20.32
FLASH_SDO4: U21.2, U25.32
FLASH_SDO5: U26.2, U30.32
FLASH_SDO6: U31.2, U35.32
FLASH_SDO7: U36.2, U40.32
FLASH_SDO8: U41.2, U45.32
FLASH_SDO9: U46.2, U50.32
FLASH_SDO10: U51.2, U55.32
FLASH_SDO11: U56.2, U60.32
FLASH_SDO12: U61.2, U65.32
FLASH_SDO13: U66.2, U70.32
FLASH_SDO14: U71.2, U75.32
FLASH_SDO15: U76.2, U80.32
FLASH_SDO16: U81.2, U85.32
FLASH_SDO17: U86.2, U90.32
FLASH_SDO18: U91.2, U95.32
FLASH_SDO19: U96.2, U100.32
FLASH_SHD: U2.28, U5.7
FLASH_SHD1: U6.7, U10.28
FLASH_SHD2: U11.7, U15.28
FLASH_SHD3: U16.7, U20.28
FLASH_SHD4: U21.7, U25.28
FLASH_SHD5: U26.7, U30.28
FLASH_SHD6: U31.7, U35.28
FLASH_SHD7: U36.7, U40.28
FLASH_SHD8: U41.7, U45.28
FLASH_SHD9: U46.7, U50.28
FLASH_SHD10: U51.7, U55.28
FLASH_SHD11: U56.7, U60.28
FLASH_SHD12: U61.7, U65.28
FLASH_SHD13: U66.7, U70.28
FLASH_SHD14: U71.7, U75.28
FLASH_SHD15: U76.7, U80.28
FLASH_SHD16: U81.7, U85.28
FLASH_SHD17: U86.7, U90.28
FLASH_SHD18: U91.7, U95.28
FLASH_SHD19: U96.7, U100.28
FLASH_SWP: U2.29, U5.3
FLASH_SWP1: U6.3, U10.29
FLASH_SWP2: U11.3, U15.29
FLASH_SWP3: U16.3, U20.29
FLASH_SWP4: U21.3, U25.29
FLASH_SWP5: U26.3, U30.29
FLASH_SWP6: U31.3, U35.29
FLASH_SWP7: U36.3, U40.29
FLASH_SWP8: U41.3, U45.29
FLASH_SWP9: U46.3, U50.29
FLASH_SWP10: U51.3, U55.29
FLASH_SWP11: U56.3, U60.29
FLASH_SWP12: U61.3, U65.29
FLASH_SWP13: U66.3, U70.29
FLASH_SWP14: U71.3, U75.29
FLASH_SWP15: U76.3, U80.29
FLASH_SWP16: U81.3, U85.29
FLASH_SWP17: U86.3, U90.29
FLASH_SWP18: U91.3, U95.29
FLASH_SWP19: U96.3, U100.29
FLASH_VDD: C24.1, SJ3.1, U2.26
FLASH_VDD1: C50.1, SJ4.1, U10.26
FLASH_VDD2: C77.1, SJ7.1, U15.26
FLASH_VDD3: C104.1, SJ10.1, U20.26
FLASH_VDD4: C131.1, SJ13.1, U25.26
FLASH_VDD5: C158.1, SJ16.1, U30.26
FLASH_VDD6: C185.1, SJ19.1, U35.26
FLASH_VDD7: C212.1, SJ22.1, U40.26
FLASH_VDD8: C239.1, SJ25.1, U45.26
FLASH_VDD9: C266.1, SJ28.1, U50.26
FLASH_VDD10: C293.1, SJ31.1, U55.26
FLASH_VDD11: C320.1, SJ34.1, U60.26
FLASH_VDD12: C347.1, SJ37.1, U65.26
FLASH_VDD13: C374.1, SJ40.1, U70.26
FLASH_VDD14: C401.1, SJ43.1, U75.26
FLASH_VDD15: C428.1, SJ46.1, U80.26
FLASH_VDD16: C455.1, SJ49.1, U85.26
FLASH_VDD17: C482.1, SJ52.1, U90.26
FLASH_VDD18: C509.1, SJ55.1, U95.26
FLASH_VDD19: C536.1, SJ58.1, U100.26
GND: C3.1, C4.1, C5.1, C6.2, C7.2, C9.1, C10.2, C11.2, C12.2, C13.2, C14.2, C15.2, C16.2, C17.2, C18.2, C19.2, C20.2, C21.2, C22.2, C23.2, C24.2, C25.2, C26.1, D3.C, E1.GND, E1.GND2, J1.1, J1.4, J2.1, J2.4, J2.20, JP2.1, JP15.GND, L1.2, L2.2, R5.1, R6.1, R7.1, R8.1, S1.1, S1.2, S2.1, S2.2, U1.2, U2.EP, U3.2, U4.6, U4.16, U5.4, Y1.2, Y1.4
GND1: C28.1, C29.1, C32.1, C33.2, C35.2, C36.2, C37.2, C38.2, C39.2, C40.2, C41.2, C42.2, C43.2, C44.2, C45.2, C46.2, C47.2, C48.2, C49.2, C50.2, C51.2, C52.1, C53.1, D7.C, E2.GND, E2.GND2, J3.1, J3.4, J4.1, J4.4, J4.20, JP1.GND, JP3.1, L3.2, L4.2, R16.1, R20.1, R21.1, R25.1, S3.1, S3.2, S4.1, S4.2, U6.4, U7.6, U7.16, U8.2, U9.2, U10.EP, Y3.2, Y3.4
GND2: C55.1, C56.1, C59.1, C60.2, C62.2, C63.2, C64.2, C65.2, C66.2, C67.2, C68.2, C69.2, C70.2, C71.2, C72.2, C73.2, C74.2, C75.2, C76.2, C77.2, C78.2, C79.1, C80.1, D11.C, E3.GND, E3.GND2, J5.1, J5.4, J6.1, J6.4, J6.20, JP4.GND, JP5.1, L5.2, L6.2, R31.1, R33.1, R34.1, R38.1, S5.1, S5.2, S6.1, S6.2, U11.4, U12.6, U12.16, U13.2, U14.2, U15.EP, Y5.2, Y5.4
GND3: C82.1, C83.1, C86.1, C87.2, C89.2, C90.2, C91.2, C92.2, C93.2, C94.2, C95.2, C96.2, C97.2, C98.2, C99.2, C100.2, C101.2, C102.2, C103.2, C104.2, C105.2, C106.1, C107.1, D15.C, E4.GND, E4.GND2, J7.1, J7.4, J8.1, J8.4, J8.20, JP6.GND, JP7.1, L7.2, L8.2, R44.1, R46.1, R47.1, R51.1, S7.1, S7.2, S8.1, S8.2, U16.4, U17.6, U17.16, U18.2, U19.2, U20.EP, Y7.2, Y7.4
GND4: C109.1, C110.1, C113.1, C114.2, C116.2, C117.2, C118.2, C119.2, C120.2, C121.2, C122.2, C123.2, C124.2, C125.2, C126.2, C127.2, C128.2, C129.2, C130.2, C131.2, C132.2, C133.1, C134.1, D19.C, E5.GND, E5.GND2, J9.1, J9.4, J10.1, J10.4, J10.20, JP8.GND, JP9.1, L9.2, L10.2, R57.1, R59.1, R60.1, R64.1, S9.1, S9.2, S10.1, S10.2, U21.4, U22.6, U22.16, U23.2, U24.2, U25.EP, Y9.2, Y9.4
GND5: C136.1, C137.1, C140.1, C141.2, C143.2, C144.2, C145.2, C146.2, C147.2, C148.2, C149.2, C150.2, C151.2, C152.2, C153.2, C154.2, C155.2, C156.2, C157.2, C158.2, C159.2, C160.1, C161.1, D23.C, E6.GND, E6.GND2, J11.1, J11.4, J12.1, J12.4, J12.20, JP10.GND, JP11.1, L11.2, L12.2, R70.1, R72.1, R73.1, R77.1, S11.1, S11.2, S12.1, S12.2, U26.4, U27.6, U27.16, U28.2, U29.2, U30.EP, Y11.2, Y11.4
GND6: C163.1, C164.1, C167.1, C168.2, C170.2, C171.2, C172.2, C173.2, C174.2, C175.2, C176.2, C177.2, C178.2, C179.2, C180.2, C181.2, C182.2, C183.2, C184.2, C185.2, C186.2, C187.1, C188.1, D27.C, E7.GND, E7.GND2, J13.1, J13.4, J14.1, J14.4, J14.20, JP12.GND, JP13.1, L13.2, L14.2, R83.1, R85.1, R86.1, R90.1, S13.1, S13.2, S14.1, S14.2, U31.4, U32.6, U32.16, U33.2, U34.2, U35.EP, Y13.2, Y13.4
GND7: C190.1, C191.1, C194.1, C195.2, C197.2, C198.2, C199.2, C200.2, C201.2, C202.2, C203.2, C204.2, C205.2, C206.2, C207.2, C208.2, C209.2, C210.2, C211.2, C212.2, C213.2, C214.1, C215.1, D31.C, E8.GND, E8.GND2, J15.1, J15.4, J16.1, J16.4, J16.20, JP14.GND, JP16.1, L15.2, L16.2, R96.1, R98.1, R99.1, R103.1, S15.1, S15.2, S16.1, S16.2, U36.4, U37.6, U37.16, U38.2, U39.2, U40.EP, Y15.2, Y15.4
GND8: C217.1, C218.1, C221.1, C222.2, C224.2, C225.2, C226.2, C227.2, C228.2, C229.2, C230.2, C231.2, C232.2, C233.2, C234.2, C235.2, C236.2, C237.2, C238.2, C239.2, C240.2, C241.1, C242.1, D35.C, E9.GND, E9.GND2, J17.1, J17.4, J18.1, J18.4, J18.20, JP17.GND, JP18.1, L17.2, L18.2, R109.1, R111.1, R112.1, R116.1, S17.1, S17.2, S18.1, S18.2, U41.4, U42.6, U42.16, U43.2, U44.2, U45.EP, Y17.2, Y17.4
GND9: C244.1, C245.1, C248.1, C249.2, C251.2, C252.2, C253.2, C254.2, C255.2, C256.2, C257.2, C258.2, C259.2, C260.2, C261.2, C262.2, C263.2, C264.2, C265.2, C266.2, C267.2, C268.1, C269.1, D39.C, E10.GND, E10.GND2, J19.1, J19.4, J20.1, J20.4, J20.20, JP19.GND, JP20.1, L19.2, L20.2, R122.1, R124.1, R125.1, R129.1, S19.1, S19.2, S20.1, S20.2, U46.4, U47.6, U47.16, U48.2, U49.2, U50.EP, Y19.2, Y19.4
GND10: C271.1, C272.1, C275.1, C276.2, C278.2, C279.2, C280.2, C281.2, C282.2, C283.2, C284.2, C285.2, C286.2, C287.2, C288.2, C289.2, C290.2, C291.2, C292.2, C293.2, C294.2, C295.1, C296.1, D43.C, E11.GND, E11.GND2, J21.1, J21.4, J22.1, J22.4, J22.20, JP21.GND, JP22.1, L21.2, L22.2, R135.1, R137.1, R138.1, R142.1, S21.1, S21.2, S22.1, S22.2, U51.4, U52.6, U52.16, U53.2, U54.2, U55.EP, Y21.2, Y21.4
GND11: C298.1, C299.1, C302.1, C303.2, C305.2, C306.2, C307.2, C308.2, C309.2, C310.2, C311.2, C312.2, C313.2, C314.2, C315.2, C316.2, C317.2, C318.2, C319.2, C320.2, C321.2, C322.1, C323.1, D47.C, E12.GND, E12.GND2, J23.1, J23.4, J24.1, J24.4, J24.20, JP23.GND, JP24.1, L23.2, L24.2, R148.1, R150.1, R151.1, R155.1, S23.1, S23.2, S24.1, S24.2, U56.4, U57.6, U57.16, U58.2, U59.2, U60.EP, Y23.2, Y23.4
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
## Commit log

2016-04-11 Initial commit of hardware
2016-04-11 Cleaning up schematic.
2016-04-21 Adding PROD_IDs to new parts, adding new parts to temp library.
2016-04-21 Misc changes after running through checklist.
2016-04-22 Adding name, value to C1, C2. Updating IC value.
2016-05-13 Fixing NPN pin assignments, flash HD and SWP pin routes.
2016-05-17 Swapping ESP32 in for ESP31B, adding pull-up to GPIO0
2016-05-25 Fixing reset pin wiring.
2016-06-13 Added GPIO0 pullup
2016-09-14 Fixing ESP32 pin map, re-routing RX, TX
2016-09-15 Re-routing i/o traces to get better ground fill.
2016-09-15 Optimizing some routing.
2016-09-15 Post-review fixes - changed C18 to 100pF
2016-09-15 Post-checklist fixes.
2016-09-16 Fixing v03 checklist issues.
2016-10-06 Upping to v10, fixing some silk.
2016-10-06 Fixing label, SJ3 silk, reinforcing connection on USB ground.
2016-10-27 Add license
2016-10-27 Updating README to standard.
2016-11-03 panel
2023-03-18 provide kicad symbol and footprint based on
    - https://cdn.sparkfun.com/assets/f/f/7/2/d/SparkFun_ESP32_Thing_-_Board_Dimensions.png
    - https://cdn.sparkfun.com/assets/learn_tutorials/5/0/7/esp32-thing-schematic.pdf
    - https://cdn.sparkfun.com/assets/learn_tutorials/5/0/7/ESP32ThingV1a.pdf
    this implements #4
